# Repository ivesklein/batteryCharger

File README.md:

# batteryCharger
Logic to charge a battery based on the voltages defined

# Protocols

## Program the Attiny85
### Preconfig
- In preferences inside the arduino IDE add: `https://raw.githubusercontent.com/digistump/arduino-boards-index/master/package_digistump_index.json`
- Install the `Digistump AVR Boards` in the boards manager
- Choose board: `Digistump AVR Boards > Digispark (Default - 16.5mhz)`
- Choose Programmer: `Micronucleus`
### Upload
Pin 5 is reset when pulled down so it will interfere with the upload
- Press Upload Code
- Connect usb and power up battery 1 at the same time

## Voltage Sensors Calibration
To calibrate the sensors:
- Add logging to the code to show the raw analog input values
- Feed the input voltage with sifferent voltages and write down the voltage and the input value
- Make a linear regresion and add the A and B values to the code
- To calibrate the output side change the code to set thr output always in HIGH
- Change the voltage on the voltage regulator and write down the voltage and input value for several voltages
-  Make a linear regresion and add the A and B values to the code

## To Calibrate the voltage regulator
- Change the code to output always HIGH
- Connect the input voltage
- Match the voltage regulator voltage with the output voltage
- Connect the output with a current meter
- Start increasing the voltage until it matches the maximum desired current
  - Decrease the current until it starts to change the current values and return to the desired value
- If increasing the voltage does not increase the current then increase the current screw
- Disconnect the output
- Change the voltage to the desired value

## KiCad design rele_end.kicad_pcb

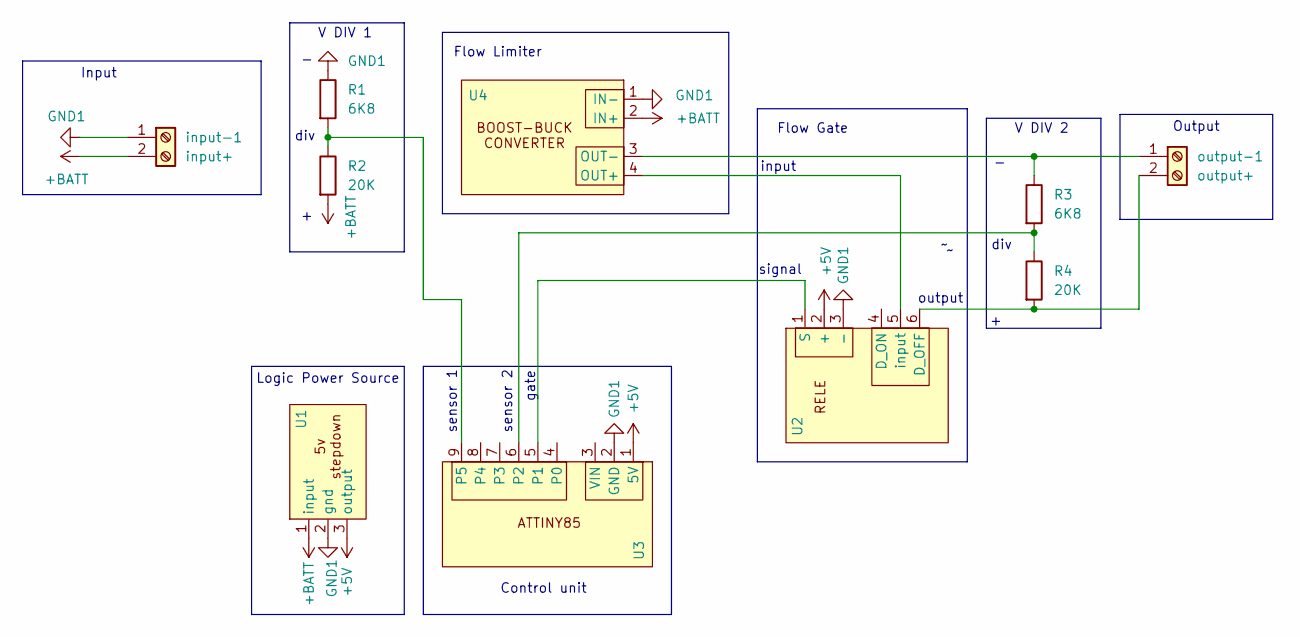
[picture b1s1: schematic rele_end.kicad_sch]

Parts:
R1, R3: 6K8; R_Axial_DIN0207_L6.3mm_D2.5mm_P7.62mm_Horizontal
R2, R4: 20K; R_Axial_DIN0207_L6.3mm_D2.5mm_P7.62mm_Horizontal
U1: DD4012SA-5V
U2: rele_board
U3: attiny85-digi
U4: SH-PWS14-1
input-1: input+; TerminalBlock_Phoenix_MKDS-1,5-2-5.08_1x02_P5.08mm_Horizont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
output-1: output+; TerminalBlock_Phoenix_MKDS-1,5-2-5.08_1x02_P5.08mm_Horizont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

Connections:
GND1: R1.1, U1.2 (gnd), U2.3 (-), U3.2 (GND), U4.1 (IN-), input-1.1
unnamed: R2.2, U1.1 (input), U4.2 (IN+), input-1.2
unnamed: U1.3 (output), U2.2 (+), U3.1 (5V)
unnamed: R4.2, U2.6 (D_OFF), output-1.2
unnamed: U2.1 (S), U3.5 (P1)
unnamed: U2.5 (input), U4.4 (OUT+)
unnamed: R3.2, R4.1, U3.6 (P2)
unnamed: R1.2, R2.1, U3.9 (P5)
unnamed: R3.1, U4.3 (OUT-), output-1.1

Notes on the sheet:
output
Logic Power Source
input
V DIV 2
V DIV 1
sensor 1
gate
div
signal
Flow Gate
Input
Flow Limiter
Control unit
Output
sensor 2

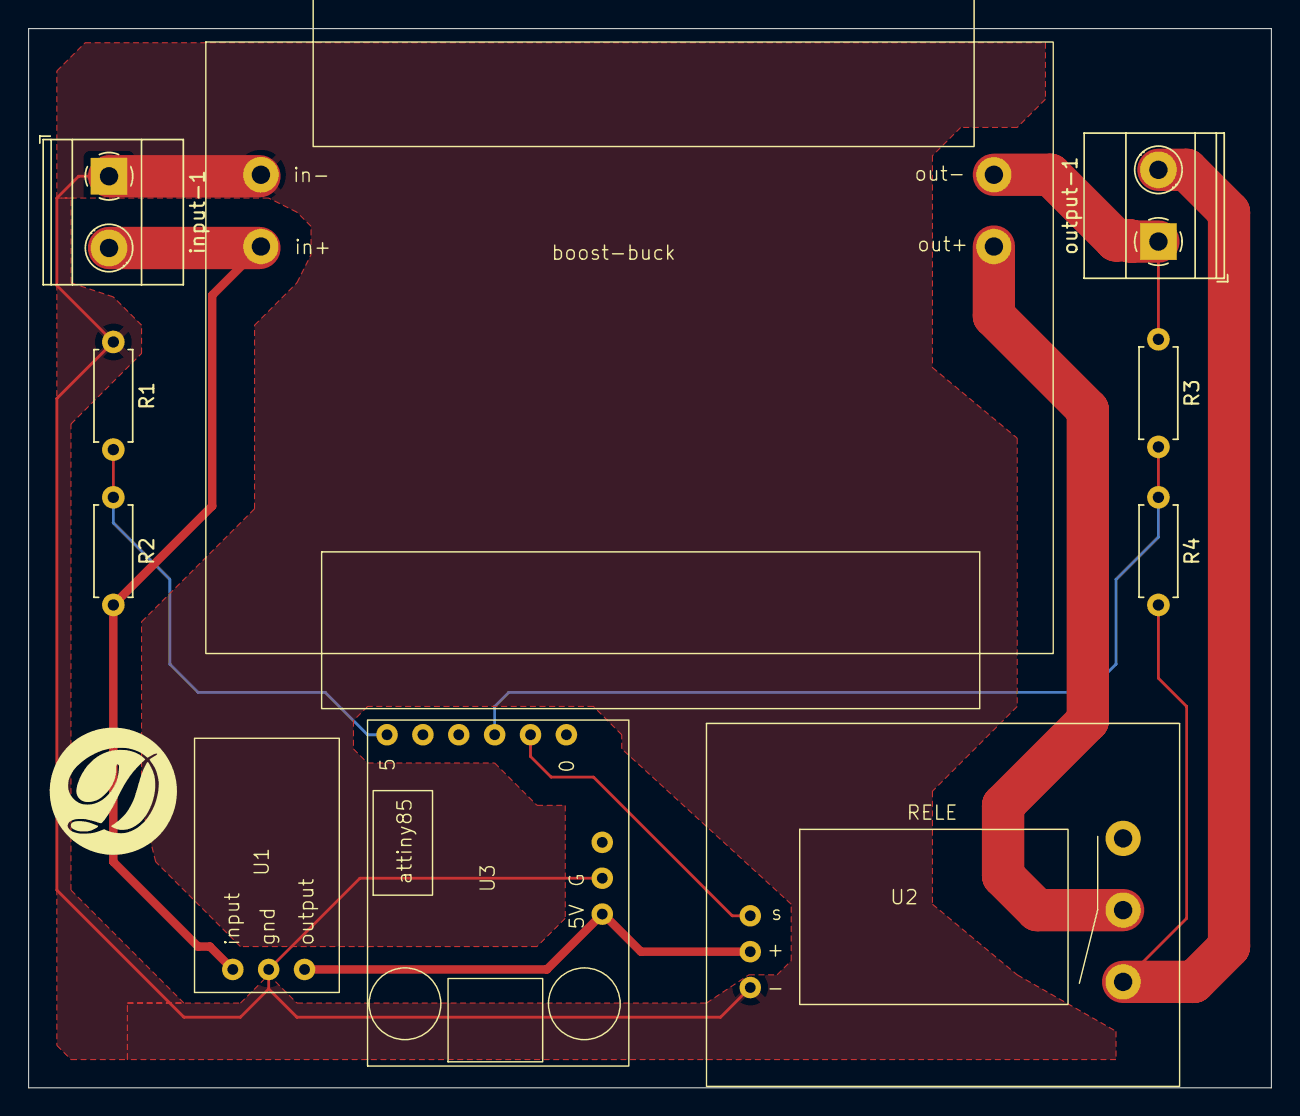
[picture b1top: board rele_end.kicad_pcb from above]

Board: 2 copper layers, 88.0 x 75.0 mm, 10 parts (0 on the bottom side), 9 nets.

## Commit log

2024-12-24 base code
2024-12-25 pcb files
2024-12-25 Rename charger.ino to overflowCharger.ino
